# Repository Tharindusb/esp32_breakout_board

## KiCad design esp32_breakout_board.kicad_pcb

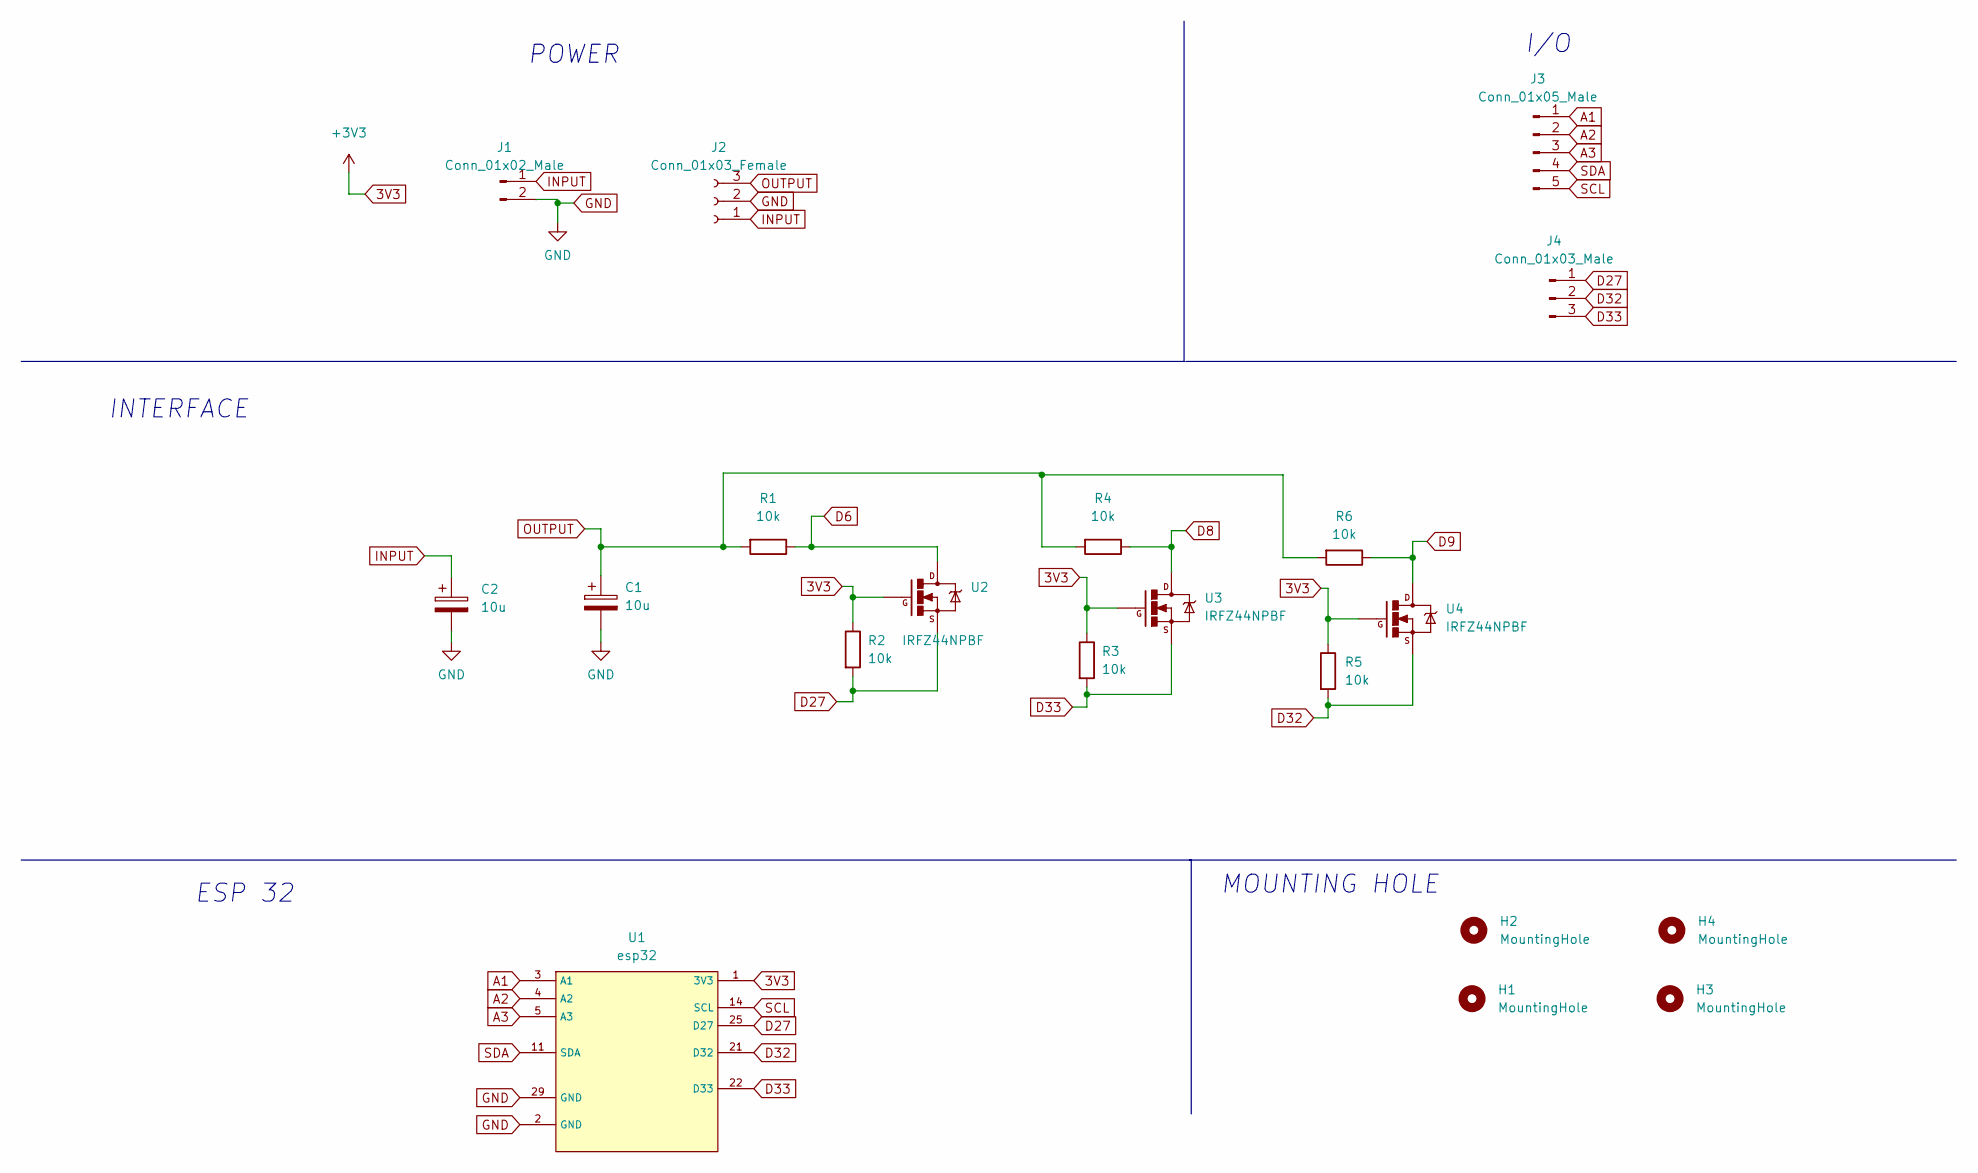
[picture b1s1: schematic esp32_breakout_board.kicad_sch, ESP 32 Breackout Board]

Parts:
C1, C2: 10u; CP_Radial_D5.0mm_P2.00mm
H1, H2, H3, H4: MountingHole; MountingHole_3.2mm_M3
J1: Conn_01x02_Male; PinHeader_1x02_P2.54mm_Vertical
J2: Conn_01x03_Female; PinSocket_1x03_P2.54mm_Vertical
J3: Conn_01x05_Male; PinHeader_1x05_P2.54mm_Vertical
J4: Conn_01x03_Male; PinHeader_1x03_P2.54mm_Vertical
R1, R2, R3, R4, R5, R6: 10k; R_Axial_DIN0204_L3.6mm_D1.6mm_P7.62mm_Horizontal
U1: esp32; MODULE_ESP32_DEVKIT_V1
U2, U3, U4: IRFZ44NPBF; TO-220

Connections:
3V3: R2.1, R3.1, R5.1, U1.1 (3V3), U2.1, U3.1, U4.1
A1: J3.1, U1.3 (A1)
A2: J3.2, U1.4 (A2)
A3: J3.3, U1.5 (A3)
D6: R1.1, U2.2
D8: R4.1, U3.2
D9: R6.1, U4.2
D27: J4.1, R2.2, U1.25 (D27), U2.3
D32: J4.2, R5.2, U1.21 (D32), U4.3
D33: J4.3, R3.2, U1.22 (D33), U3.3
GND: C1.2, C2.2, J1.2, J2.2, U1.2 (GND), U1.29 (GND)
INPUT: C2.1, J1.1, J2.1
OUTPUT: C1.1, J2.3, R1.2, R4.2, R6.2
SCL: J3.5, U1.14 (SCL)
SDA: J3.4, U1.11 (SDA)

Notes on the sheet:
ESP 32
I/O
POWER
INTERFACE
MOUNTING HOLE

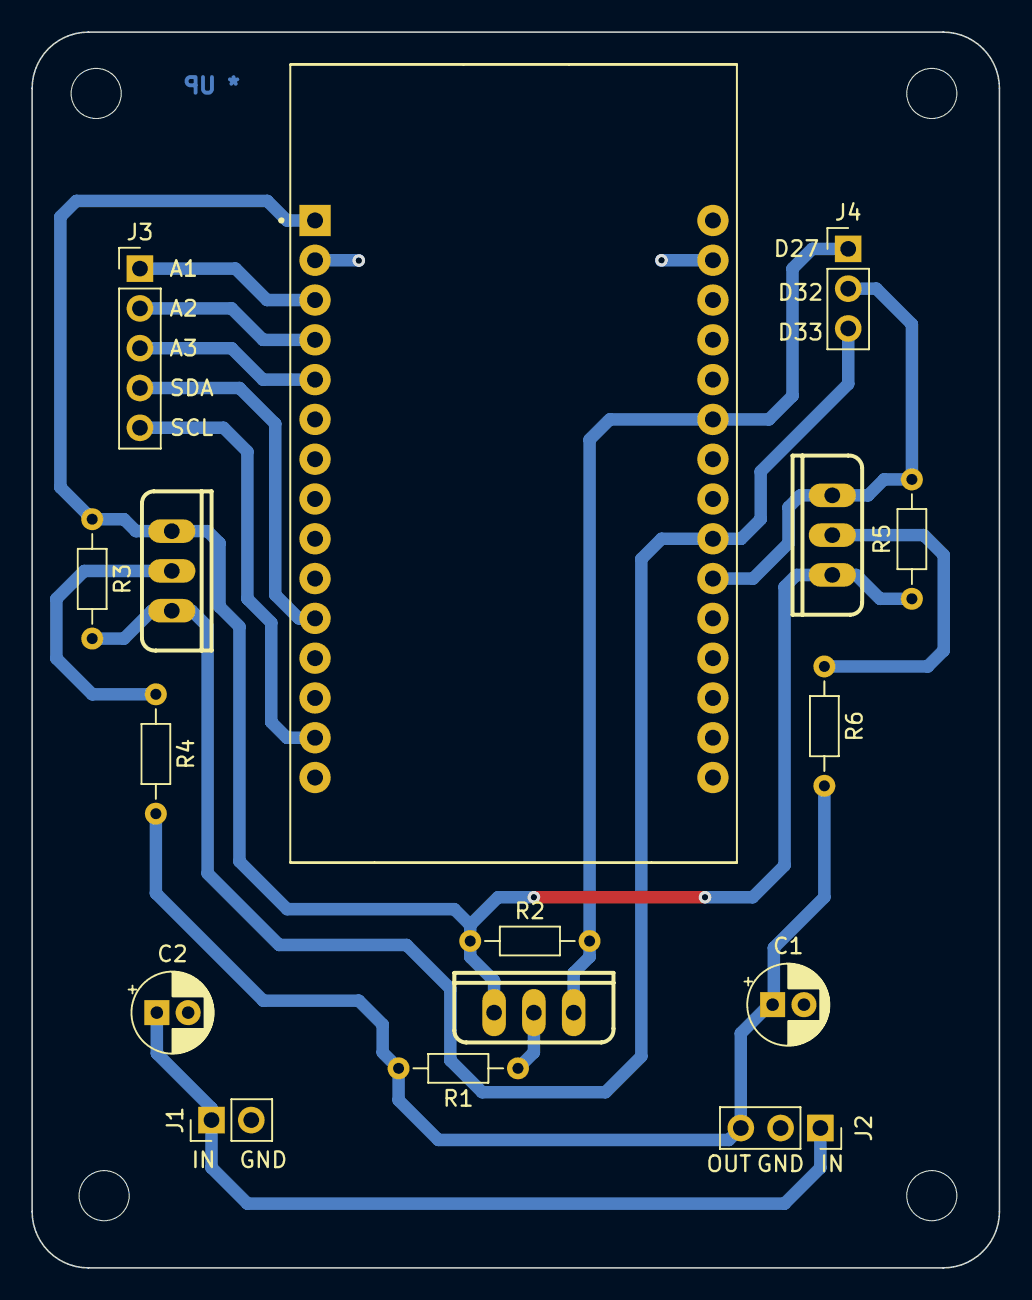
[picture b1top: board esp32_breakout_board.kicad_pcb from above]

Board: 2 copper layers, 61.7 x 78.9 mm, 20 parts (0 on the bottom side), 15 nets.

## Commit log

2022-08-12 Esp 32
